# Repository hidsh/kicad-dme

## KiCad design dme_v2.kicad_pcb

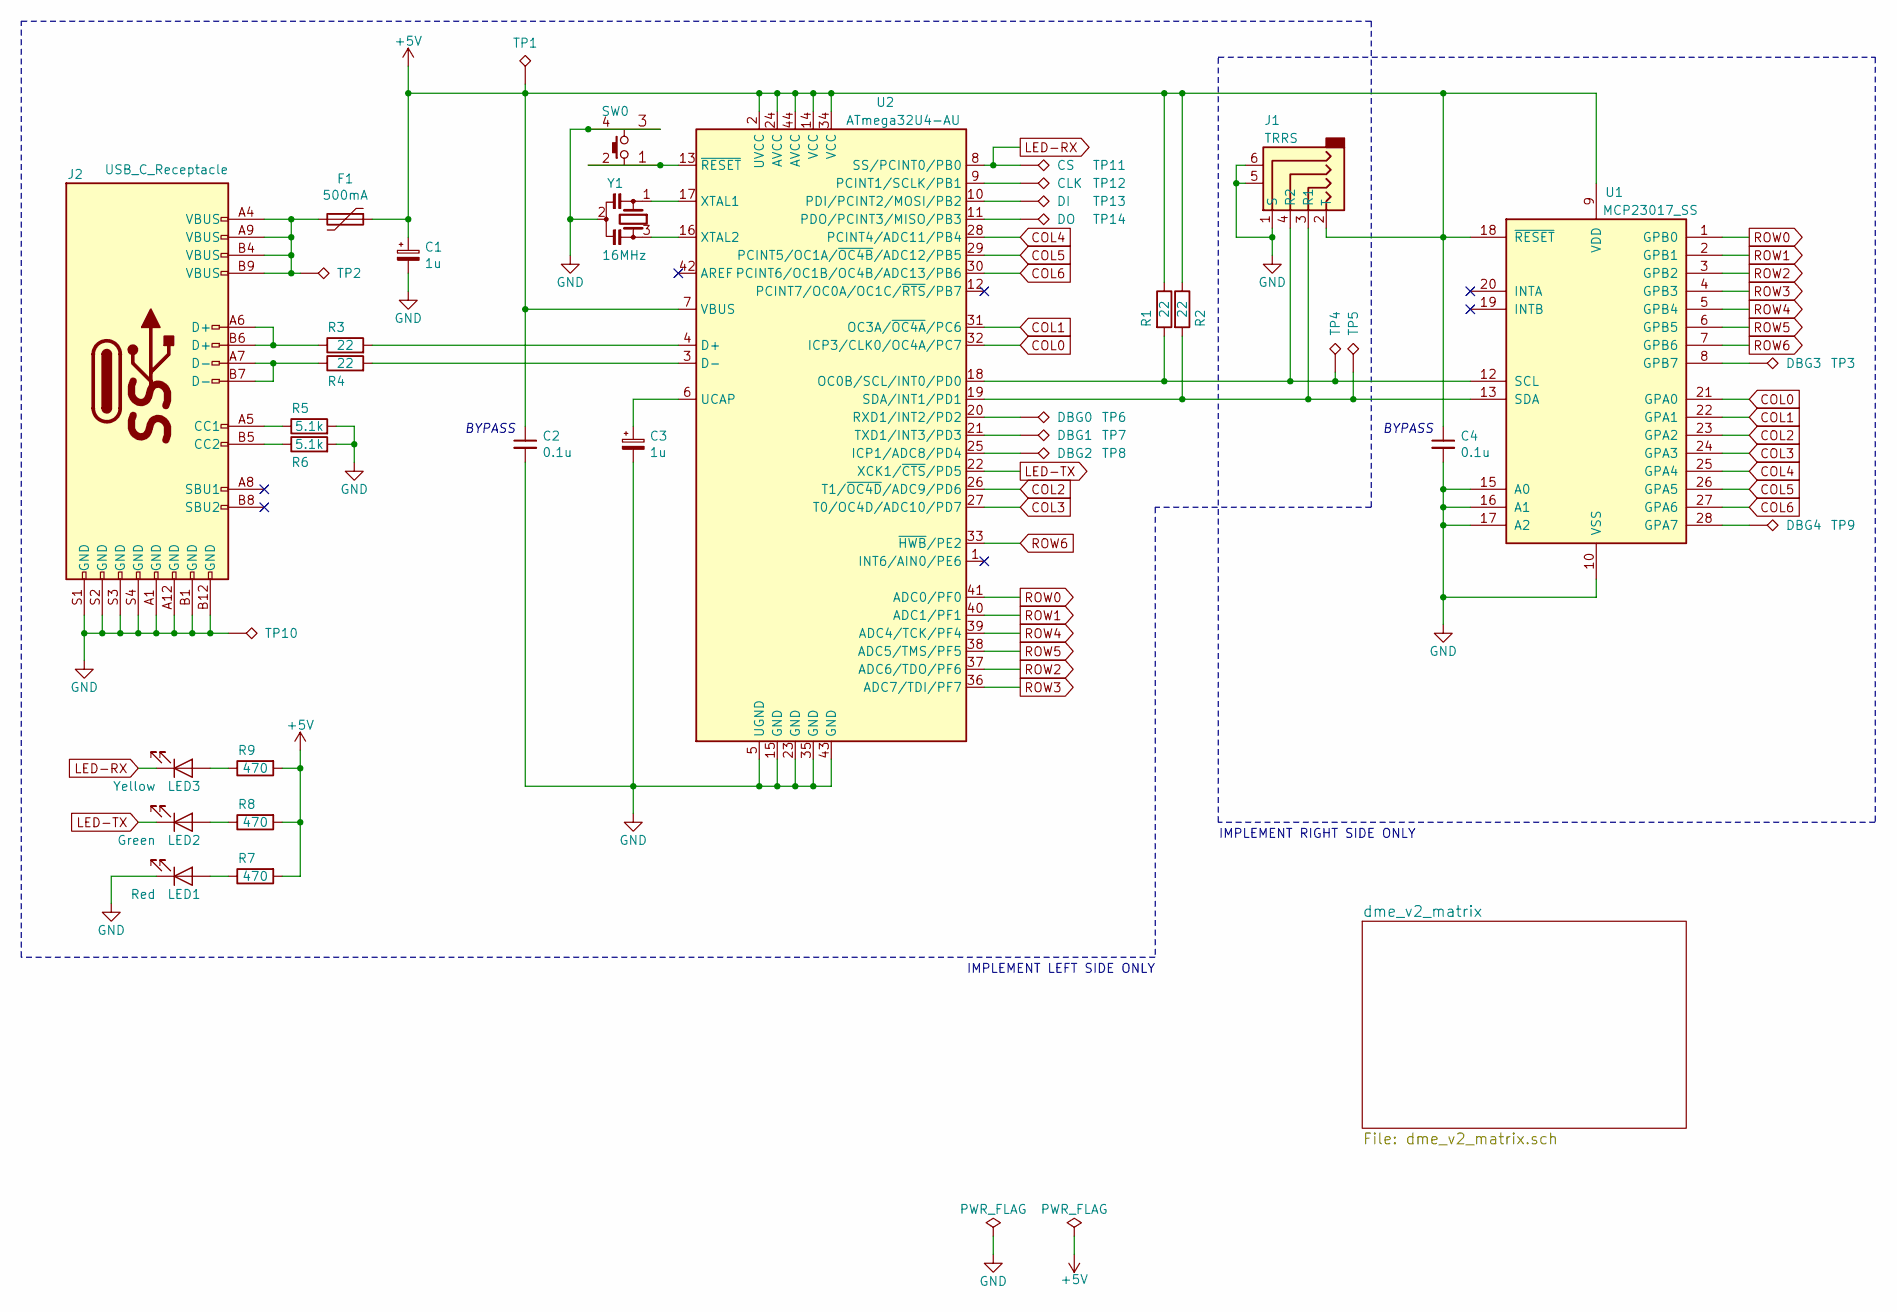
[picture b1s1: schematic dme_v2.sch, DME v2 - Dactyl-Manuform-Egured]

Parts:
C1, C3: 1u; C_0603_1608Metric
C2, C4: 0.1u; C_0603_1608Metric
F1: 500mA; Fuse_1206_3216Metric
J1: TRRS; SJ-43514-SMT
J2: USB_C_Receptacle; USB_C_Receptacle_GCT_USB4085
LED1: Red; LED_0603_1608Metric
LED2: Green; LED_0603_1608Metric
LED3: Yellow; LED_0603_1608Metric
R1, R2, R3, R4: 22; R_0603_1608Metric
R5, R6: 5.1k; R_0603_1608Metric
R7, R8, R9: 470; R_0603_1608Metric
SW0: SKRPACE010; SKRPACE010_round
TP1, TP2, TP4, TP5, TP10: CHK; TestPoint_THTPad_D1.5mm_Drill0.7mm
TP3: DBG3; TestPoint_THTPad_D1.5mm_Drill0.7mm
TP6: DBG0; TestPoint_THTPad_D1.5mm_Drill0.7mm
TP7: DBG1; TestPoint_THTPad_D1.5mm_Drill0.7mm
TP8: DBG2; TestPoint_THTPad_D1.5mm_Drill0.7mm
TP9: DBG4; TestPoint_THTPad_D1.5mm_Drill0.7mm
TP11: CS; TestPoint_THTPad_D1.5mm_Drill0.7mm
TP12: CLK; TestPoint_THTPad_D1.5mm_Drill0.7mm
TP13: DI; TestPoint_THTPad_D1.5mm_Drill0.7mm
TP14: DO; TestPoint_THTPad_D1.5mm_Drill0.7mm
U1: MCP23017_SS; SSOP-28_5.3x10.2mm_P0.65mm_round
U2: ATmega32U4-AU; TQFP-44_10x10mm_P0.8mm_round
Y1: 16MHz; Resonator_SMD_muRata_CSTxExxV-3Pin_3.0x1.1mm_HandSoldering_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

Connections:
+5V: C1.1, C2.1, C4.1, F1.1, J1.2 (T), R1.1, R2.1, R7.2, R8.2, R9.2, TP1.1, U1.9 (VDD), U1.18 (~RESET~), U2.2 (UVCC), U2.7 (VBUS), U2.14 (VCC), U2.24 (AVCC), U2.34 (VCC), U2.44 (AVCC)
COL0: U1.21 (GPA0), U2.32 (ICP3/CLK0/OC4A/PC7); also elsewhere on the board
COL1: U1.22 (GPA1), U2.31 (OC3A/~OC4A~/PC6); also elsewhere on the board
COL2: U1.23 (GPA2), U2.26 (T1/~OC4D~/ADC9/PD6); also elsewhere on the board
COL3: U1.24 (GPA3), U2.27 (T0/OC4D/ADC10/PD7); also elsewhere on the board
COL4: U1.25 (GPA4), U2.28 (PCINT4/ADC11/PB4); also elsewhere on the board
COL5: U1.26 (GPA5), U2.29 (PCINT5/OC1A/~OC4B~/ADC12/PB5); also elsewhere on the board
COL6: U1.27 (GPA6), U2.30 (PCINT6/OC1B/OC4B/ADC13/PB6); also elsewhere on the board
GND: C1.2, C2.2, C3.2, C4.2, J1.1 (S), J1.5, J1.6, J2.A1 (GND), J2.A12 (GND), J2.B1 (GND), J2.B12 (GND), J2.S1 (GND), J2.S2 (GND), J2.S3 (GND), J2.S4 (GND), LED1.1 (K), R5.2, R6.2, SW0.3, SW0.4, TP10.1, U1.10 (VSS), U1.15 (A0), U1.16 (A1), U1.17 (A2), U2.5 (UGND), U2.15 (GND), U2.23 (GND), U2.35 (GND), U2.43 (GND), Y1.2
LED-RX: LED3.1 (K), TP11.1, U2.8 (SS/PCINT0/PB0)
LED-TX: LED2.1 (K), U2.22 (XCK1/~CTS~/PD5)
unnamed: C3.1, U2.6 (UCAP)
unnamed: F1.2, J2.A4 (VBUS), J2.A9 (VBUS), J2.B4 (VBUS), J2.B9 (VBUS), TP2.1
unnamed: J1.3 (R1), R2.2, TP5.1, U1.13 (SDA), U2.19 (SDA/INT1/PD1)
unnamed: J1.4 (R2), R1.2, TP4.1, U1.12 (SCL), U2.18 (OC0B/SCL/INT0/PD0)
unnamed: J2.A5 (CC1), R5.1
unnamed: J2.A6 (D+), J2.B6 (D+), R3.1
unnamed: J2.A7 (D-), J2.B7 (D-), R4.1
unnamed: J2.B5 (CC2), R6.1
unnamed: LED1.2 (A), R7.1
unnamed: LED2.2 (A), R8.1
unnamed: LED3.2 (A), R9.1
unnamed: R3.2, U2.4 (D+)
unnamed: R4.2, U2.3 (D-)
unnamed: SW0.1, SW0.2, U2.13 (~RESET~)
unnamed: TP3.1, U1.8 (GPB7)
unnamed: TP6.1, U2.20 (RXD1/INT2/PD2)
unnamed: TP7.1, U2.21 (TXD1/INT3/PD3)
unnamed: TP8.1, U2.25 (ICP1/ADC8/PD4)
unnamed: TP9.1, U1.28 (GPA7)
unnamed: TP12.1, U2.9 (PCINT1/SCLK/PB1)
unnamed: TP13.1, U2.10 (PDI/PCINT2/MOSI/PB2)
unnamed: TP14.1, U2.11 (PDO/PCINT3/MISO/PB3)
unnamed: U2.16 (XTAL2), Y1.3
unnamed: U2.17 (XTAL1), Y1.1
ROW0: U1.1 (GPB0), U2.41 (ADC0/PF0); also elsewhere on the board
ROW1: U1.2 (GPB1), U2.40 (ADC1/PF1); also elsewhere on the board
ROW2: U1.3 (GPB2), U2.37 (ADC6/TDO/PF6); also elsewhere on the board
ROW3: U1.4 (GPB3), U2.36 (ADC7/TDI/PF7); also elsewhere on the board
ROW4: U1.5 (GPB4), U2.39 (ADC4/TCK/PF4); also elsewhere on the board
ROW5: U1.6 (GPB5), U2.38 (ADC5/TMS/PF5); also elsewhere on the board
ROW6: U1.7 (GPB6), U2.33 (~HWB~/PE2); also elsewhere on the board

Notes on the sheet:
BYPASS
IMPLEMENT RIGHT SIDE ONLY
IMPLEMENT LEFT SIDE ONLY

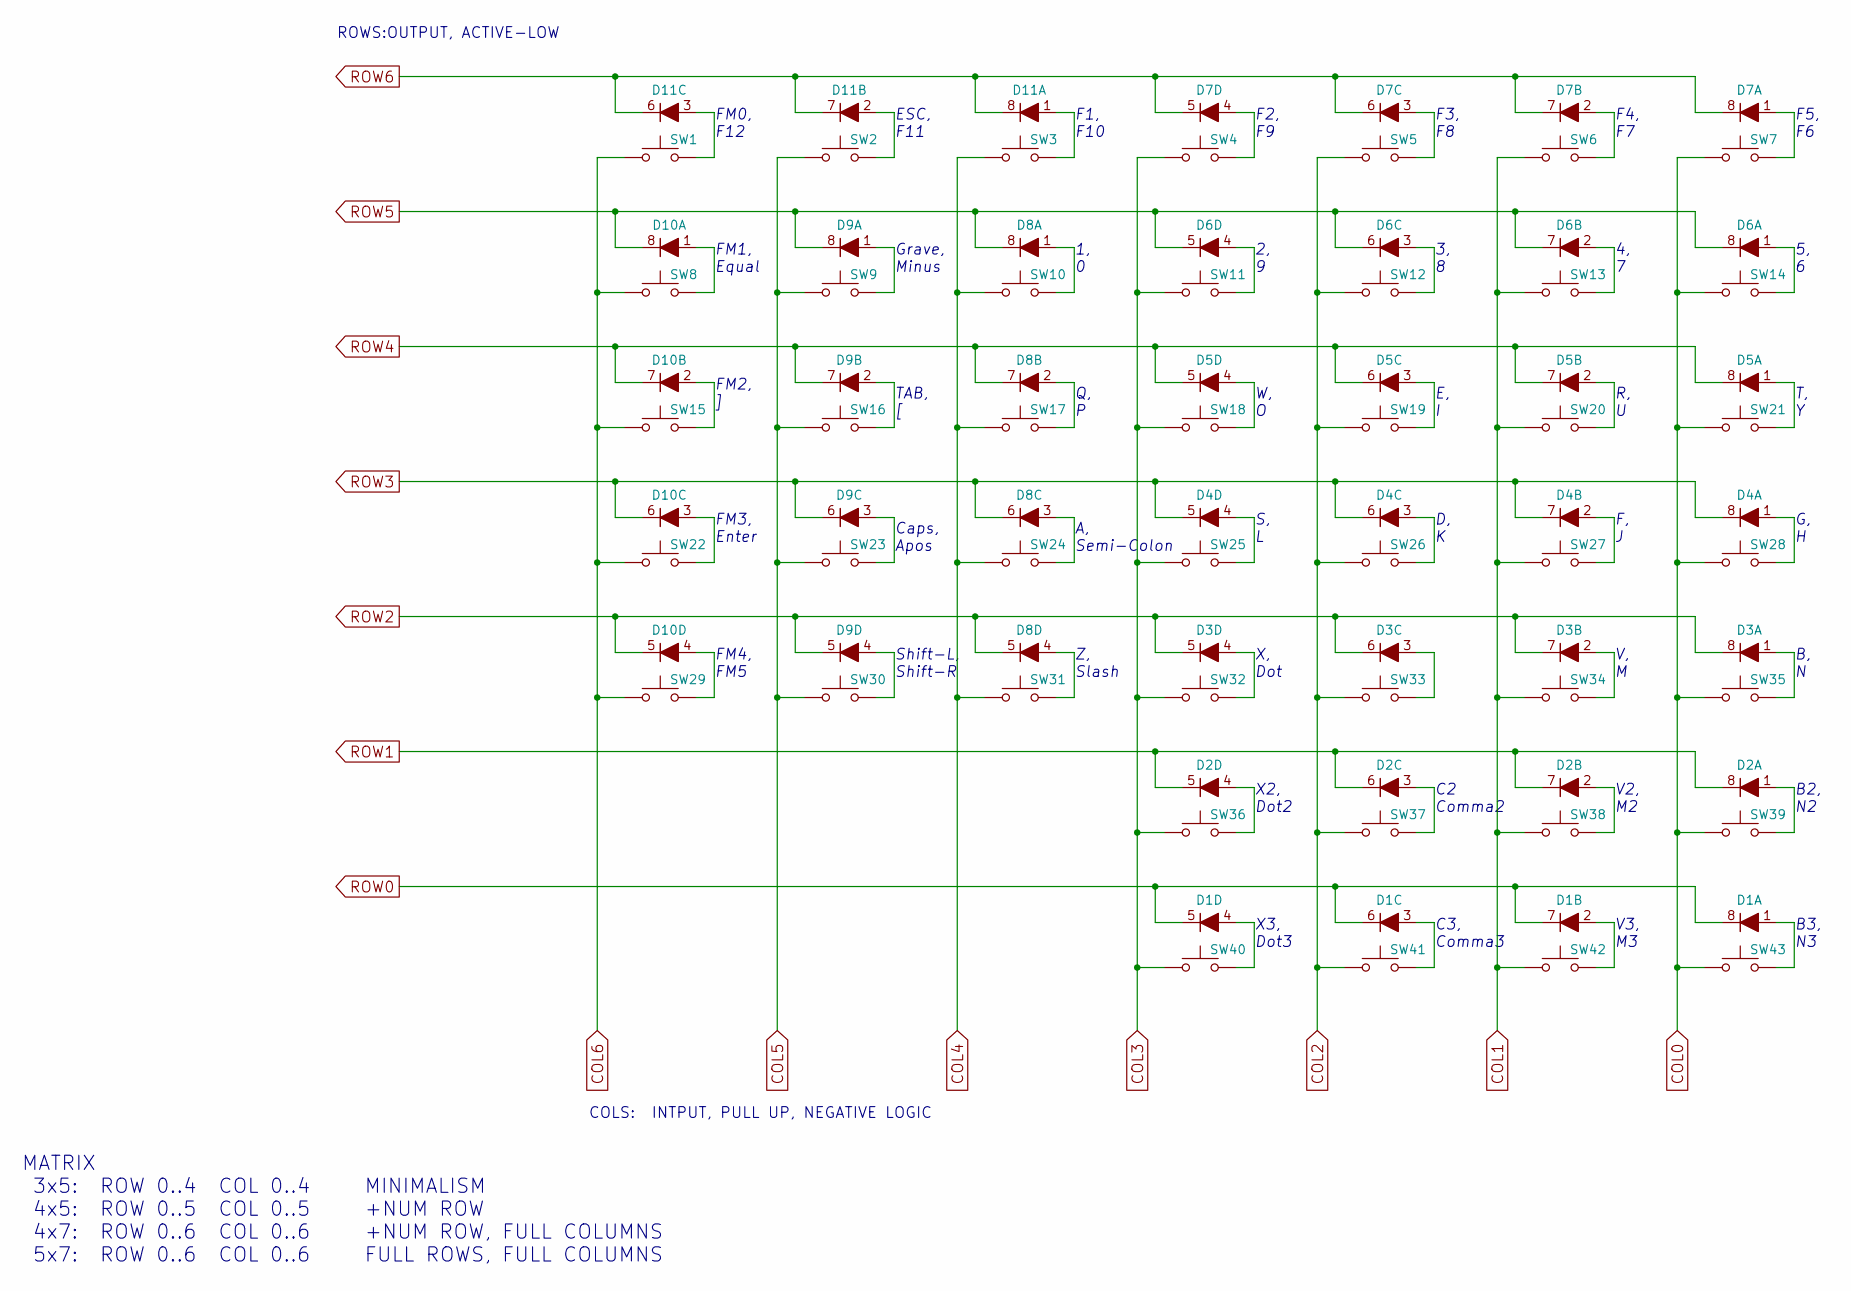
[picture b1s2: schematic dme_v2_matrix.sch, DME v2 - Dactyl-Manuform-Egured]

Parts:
D1, D2, D3, D4, D5, D6, D7, D8, D9, D10, D11: D_ALT_multi_x4; RB521ZS8A30_round
SW1, SW2, SW3, SW4, SW5, SW6, SW7, SW8, SW9, SW10, SW11, SW12, SW13, SW14, SW15, SW16, SW17, SW18, SW19, SW20, SW21, SW22, SW23, SW24, SW25, SW26, SW27, SW28, SW29, SW30, SW31, SW32, SW33, SW34, SW35, SW36, SW37, SW38, SW39, SW40, SW41, SW42, SW43: SW_Push; CHERRY_PCB_100H_oval

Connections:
COL0: SW7.1, SW14.1, SW21.1, SW28.1, SW35.1, SW39.1, SW43.1; also elsewhere on the board
COL1: SW6.1, SW13.1, SW20.1, SW27.1, SW34.1, SW38.1, SW42.1; also elsewhere on the board
COL2: SW5.1, SW12.1, SW19.1, SW26.1, SW33.1, SW37.1, SW41.1; also elsewhere on the board
COL3: SW4.1, SW11.1, SW18.1, SW25.1, SW32.1, SW36.1, SW40.1; also elsewhere on the board
COL4: SW3.1, SW10.1, SW17.1, SW24.1, SW31.1; also elsewhere on the board
COL5: SW2.1, SW9.1, SW16.1, SW23.1, SW30.1; also elsewhere on the board
COL6: SW1.1, SW8.1, SW15.1, SW22.1, SW29.1; also elsewhere on the board
unnamed: D1.1 (A1), SW43.2
unnamed: D1.2 (A2), SW42.2
unnamed: D1.3 (A3), SW41.2
unnamed: D1.4 (A4), SW40.2
unnamed: D2.1 (A1), SW39.2
unnamed: D2.2 (A2), SW38.2
unnamed: D2.3 (A3), SW37.2
unnamed: D2.4 (A4), SW36.2
unnamed: D3.1 (A1), SW35.2
unnamed: D3.2 (A2), SW34.2
unnamed: D3.3 (A3), SW33.2
unnamed: D3.4 (A4), SW32.2
unnamed: D4.1 (A1), SW28.2
unnamed: D4.2 (A2), SW27.2
unnamed: D4.3 (A3), SW26.2
unnamed: D4.4 (A4), SW25.2
unnamed: D5.1 (A1), SW21.2
unnamed: D5.2 (A2), SW20.2
unnamed: D5.3 (A3), SW19.2
unnamed: D5.4 (A4), SW18.2
unnamed: D6.1 (A1), SW14.2
unnamed: D6.2 (A2), SW13.2
unnamed: D6.3 (A3), SW12.2
unnamed: D6.4 (A4), SW11.2
unnamed: D7.1 (A1), SW7.2
unnamed: D7.2 (A2), SW6.2
unnamed: D7.3 (A3), SW5.2
unnamed: D7.4 (A4), SW4.2
unnamed: D8.1 (A1), SW10.2
unnamed: D8.2 (A2), SW17.2
unnamed: D8.3 (A3), SW24.2
unnamed: D8.4 (A4), SW31.2
unnamed: D9.1 (A1), SW9.2
unnamed: D9.2 (A2), SW16.2
unnamed: D9.3 (A3), SW23.2
unnamed: D9.4 (A4), SW30.2
unnamed: D10.1 (A1), SW8.2
unnamed: D10.2 (A2), SW15.2
unnamed: D10.3 (A3), SW22.2
unnamed: D10.4 (A4), SW29.2
unnamed: D11.1 (A1), SW3.2
unnamed: D11.2 (A2), SW2.2
unnamed: D11.3 (A3), SW1.2
ROW0: D1.5 (K4), D1.6 (K3), D1.7 (K2), D1.8 (K1); also elsewhere on the board
ROW1: D2.5 (K4), D2.6 (K3), D2.7 (K2), D2.8 (K1); also elsewhere on the board
ROW2: D3.5 (K4), D3.6 (K3), D3.7 (K2), D3.8 (K1), D8.5 (K4), D9.5 (K4), D10.5 (K4); also elsewhere on the board
ROW3: D4.5 (K4), D4.6 (K3), D4.7 (K2), D4.8 (K1), D8.6 (K3), D9.6 (K3), D10.6 (K3); also elsewhere on the board
ROW4: D5.5 (K4), D5.6 (K3), D5.7 (K2), D5.8 (K1), D8.7 (K2), D9.7 (K2), D10.7 (K2); also elsewhere on the board
ROW5: D6.5 (K4), D6.6 (K3), D6.7 (K2), D6.8 (K1), D8.8 (K1), D9.8 (K1), D10.8 (K1); also elsewhere on the board
ROW6: D7.5 (K4), D7.6 (K3), D7.7 (K2), D7.8 (K1), D11.6 (K3), D11.7 (K2), D11.8 (K1); also elsewhere on the board

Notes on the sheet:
ROWS:OUTPUT, ACTIVE-LOW
COLS: INTPUT, PULL UP, NEGATIVE LOGIC
B2, N2
V2, M2
X2, Dot2
B, N
Shift-L, Shift-R
Grave, Minus
V3, M3
B3, N3
V, M
X, Dot
G, H
F, J
D, K
S, L
Caps, Apos
T, Y
R, U
E, I
W, O
TAB, [
5, 6
4, 7
3, 8
2, 9
X3, Dot3
F5, F6
F4, F7
F3, F8
F2, F9
ESC, F11
MATRIX 3x5: ROW 0..4 COL 0..4 MINIMALISM 4x5: ROW 0..5 COL 0..5 +NUM ROW 4x7: ROW 0..6 COL 0..6 +NUM ROW, FULL COLUMNS 5x7: ROW 0..6 COL 0..6 FULL ROWS, FULL COLUMNS
FM0, F12
FM1, Equal
FM2, ]
FM3, Enter
FM4, FM5
F1, F10
1, 0

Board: 2 copper layers, 91 parts (0 on the bottom side), 85 nets, no tracks yet.

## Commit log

2019-05-25 add design
